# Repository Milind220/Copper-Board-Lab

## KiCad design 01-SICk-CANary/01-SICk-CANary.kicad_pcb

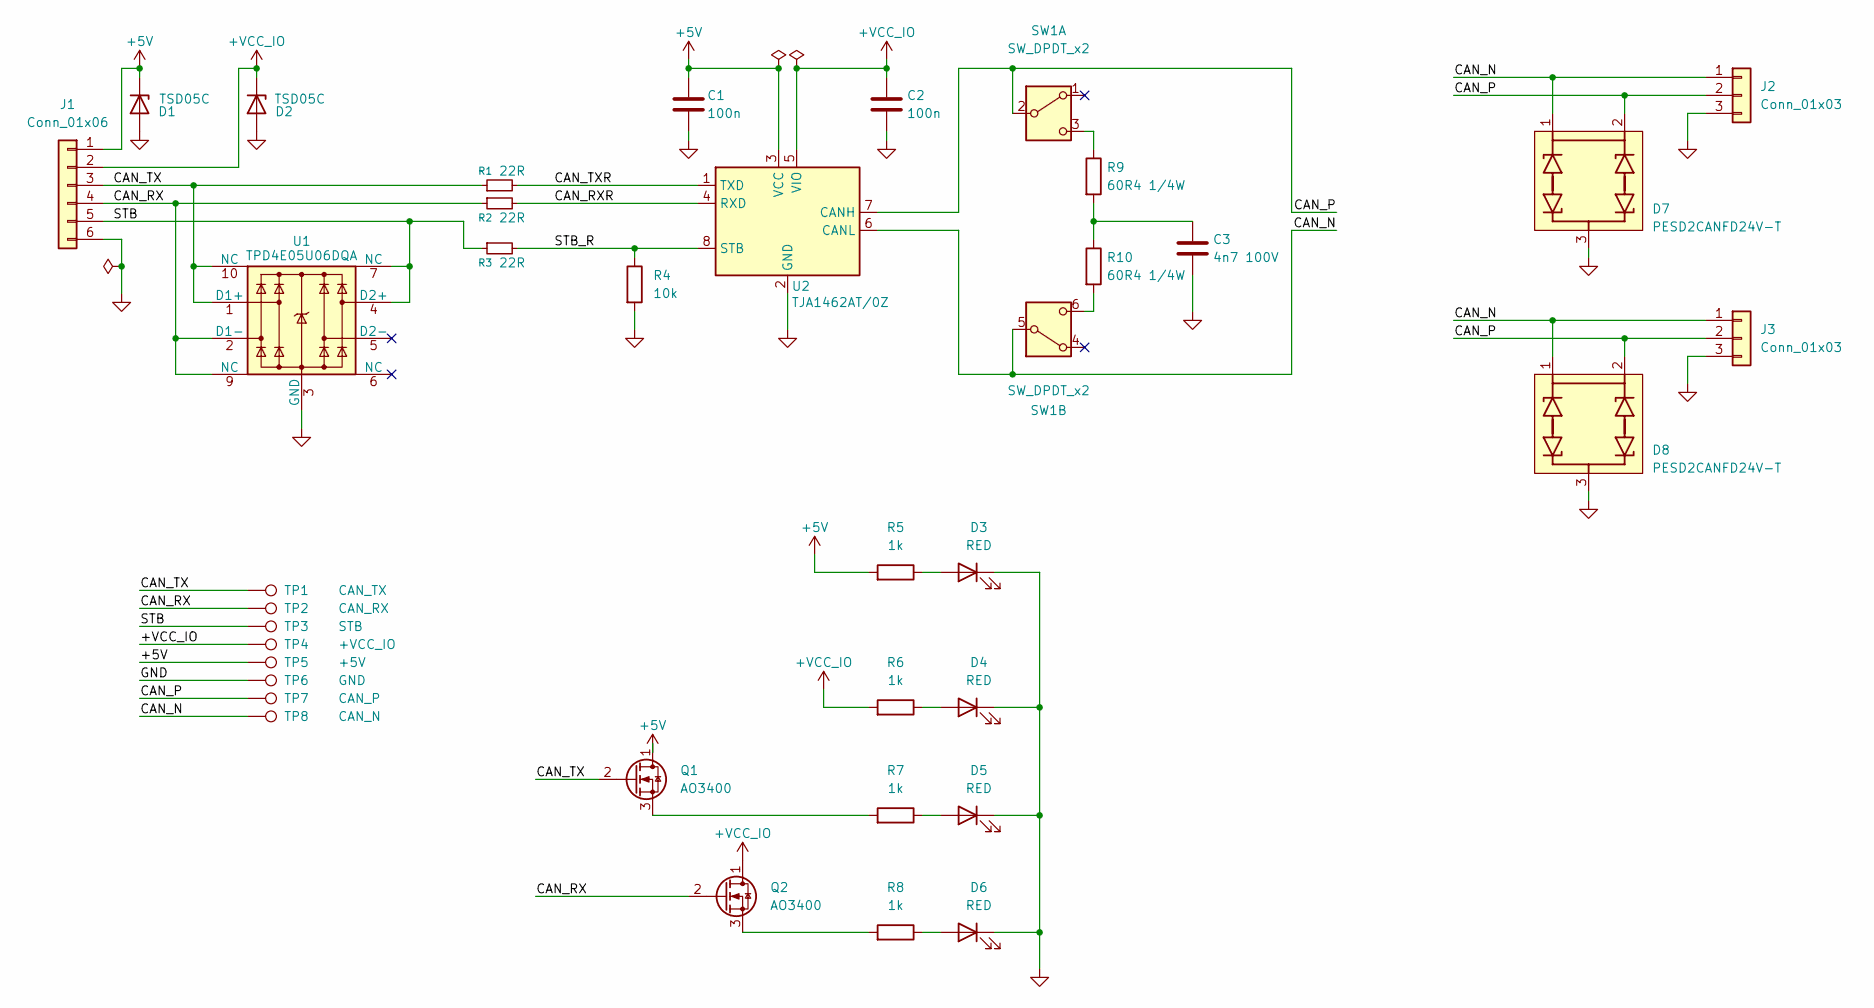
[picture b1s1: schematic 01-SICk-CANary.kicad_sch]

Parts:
C1, C2: 100n; C_0402_1005Metric
C3: 4n7 100V; C_0402_1005Metric
D1, D2: TSD05C; D_SOD-323F
D3, D4, D5, D6: RED; LED_0603_1608Metric
D7, D8: PESD2CANFD24V-T; SOT-23
J1: Conn_01x06; JST_GH_SM06B-GHS-TB_1x06-1MP_P1.25mm_Horizontal
J2, J3: Conn_01x03; PhoenixContact_MCV_1,5_3-G-3.5_1x03_P3.50mm_Vertical
Q1, Q2: AO3400; SOT-23
R1, R2, R3: 22R; R_0402_1005Metric
R4: 10k; R_0402_1005Metric
R5, R6, R7, R8: 1k; R_0402_1005Metric
R9, R10: 60R4 1/4W; R_0805_2012Metric
SW1: SW_DPDT_x2; CAS-220A
TP1: CAN_TX; TestPoint_Pad_D1.0mm
TP2: CAN_RX; TestPoint_Pad_D1.0mm
TP3: STB; TestPoint_Pad_D1.0mm
TP4: +VCC_IO; TestPoint_Pad_D1.0mm
TP5: +5V; TestPoint_Pad_D1.0mm
TP6: GND; TestPoint_Pad_D1.0mm
TP7: CAN_P; TestPoint_Pad_D1.0mm
TP8: CAN_N; TestPoint_Pad_D1.0mm
U1: TPD4E05U06DQA; USON-10_2.5x1.0mm_P0.5mm
U2: TJA1462AT/0Z; SO-8_3.9x4.9mm_P1.27mm

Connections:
+5V: C1.1, D1.1, J1.1, Q1.1 (D), R5.2, TP5.1 (1_1), U2.3 (VCC)
+VCC_IO: C2.1, D2.1, J1.2, Q2.1 (D), R6.2, TP4.1 (1_1), U2.5 (VIO)
/CAN_N: D7.1, D8.1, J2.1, J3.1, SW1.5 (B), TP8.1 (1_1), U2.6 (CANL)
/CAN_P: D7.2, D8.2, J2.2, J3.2, SW1.2 (B), TP7.1 (1_1), U2.7 (CANH)
/CAN_RX: J1.4, Q2.2 (G), R2.1, TP2.1 (1_1), U1.2 (D1-), U1.9 (NC)
/CAN_RXR: R2.2, U2.4 (RXD)
/CAN_TX: J1.3, Q1.2 (G), R1.1, TP1.1 (1_1), U1.1 (D1+), U1.10 (NC)
/CAN_TXR: R1.2, U2.1 (TXD)
/STB: J1.5, R3.1, TP3.1 (1_1), U1.4 (D2+), U1.7 (NC)
/STB_R: R3.2, R4.1, U2.8 (STB)
GND: C1.2, C2.2, C3.2, D1.2, D2.2, D3.1 (K), D4.1 (K), D5.1 (K), D6.1 (K), D7.3, D8.3, J1.6, J2.3, J3.3, R4.2, TP6.1 (1_1), U1.3 (GND), U1.8 (GND), U2.2 (GND)
unnamed: C3.1, R9.2, R10.1
unnamed: D3.2 (A), R5.1
unnamed: D4.2 (A), R6.1
unnamed: D5.2 (A), R7.1
unnamed: D6.2 (A), R8.1
unnamed: Q1.3 (S), R7.2
unnamed: Q2.3 (S), R8.2
unnamed: R9.1, SW1.3 (C)
unnamed: R10.2, SW1.6 (C)

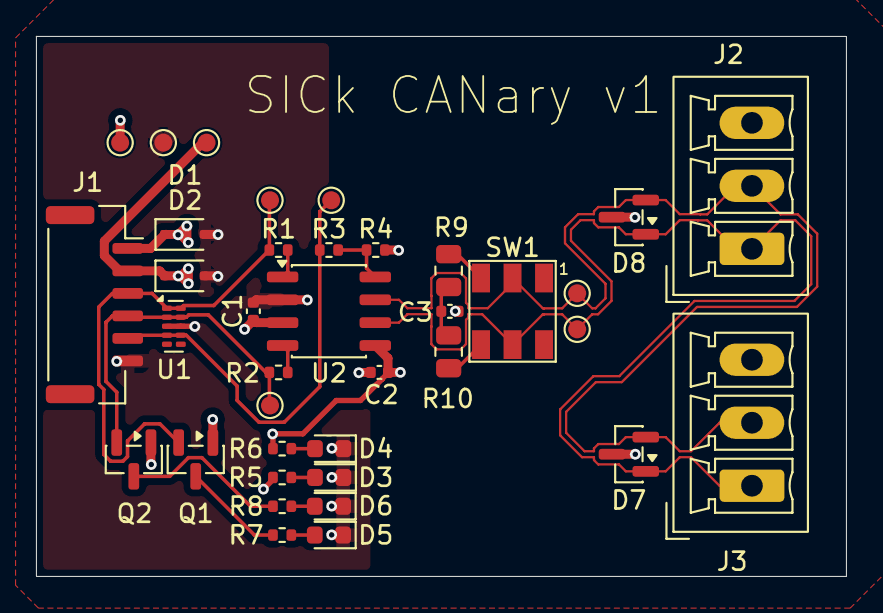
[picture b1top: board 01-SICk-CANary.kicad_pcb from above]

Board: 4 copper layers, 45.0 x 30.0 mm, 37 parts (0 on the bottom side), 20 nets.

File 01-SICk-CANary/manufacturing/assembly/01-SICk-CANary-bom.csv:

"Refs","Value","Footprint","Qty","LCSC","MPN","DNP"
"C1,C2","100n","Capacitor_SMD:C_0402_1005Metric","2","C1525","CL05B104KO5NNNC",""
"C3","4n7 100V","Capacitor_SMD:C_0402_1005Metric","1","C576733","CC0402KRX7R0BB472",""
"D1,D2","TSD05C","Diode_SMD:D_SOD-323F","2","C20611048","TSD05CDYFR",""
"D3-D6","LED","LED_SMD:LED_0603_1608Metric","4","C2286","KT-0603R",""
"D7,D8","PESD2CANFD24V-T","Package_TO_SOT_SMD:SOT-23","2","C39832198","PESD2CANFD24V-TR",""
"J1","Conn_01x06","Connector_JST:JST_GH_SM06B-GHS-TB_1x06-1MP_P1.25mm_Horizontal","1","C51940119","XY-SM06B-GHS-TB",""
"J2,J3","Conn_01x03","Connector_Phoenix_MC:PhoenixContact_MCV_1,5_3-G-3.5_1x03_P3.50mm_Vertical","2","C480579","1840379",""
"Q1,Q2","Q_NMOS_DGS","Package_TO_SOT_SMD:SOT-23","2","C20917","AO3400A",""
"R1-R3","22R","Resistor_SMD:R_0402_1005Metric","3","C25092","0402WGF220JTCE",""
"R4","10k","Resistor_SMD:R_0402_1005Metric","1","C25744","0402WGF1002TCE",""
"R5-R8","1k","Resistor_SMD:R_0402_1005Metric","4","C11702","0402WGF1001TCE",""
"R9,R10","60R4 1/4W","Resistor_SMD:R_0805_2012Metric","2","C2481607","RK73H2ATTD60R4F",""
"SW1","SW_DPDT_x2","0_Nidec_CAS:CAS-220A","1","C3664537","CAS-220A1",""
"U1","TPD4E05U06DQA","Package_SON:USON-10_2.5x1.0mm_P0.5mm","1","C138714","TPD4E05U06DQAR",""
"U2","TJA1462AT/0Z","Package_SO:SO-8_3.9x4.9mm_P1.27mm","1","C3234095","TJA1462AT/0Z",""

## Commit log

2026-05-23 feat: add SICk CANary schematic
2026-05-23 feat: add SICk CANary PCB layout
2026-05-23 chore: add SICk CANary assembly outputs
2026-05-23 chore: add KiCad gitignore
2026-05-23 chore: update board files
2026-05-23 feat: finish PCB design
